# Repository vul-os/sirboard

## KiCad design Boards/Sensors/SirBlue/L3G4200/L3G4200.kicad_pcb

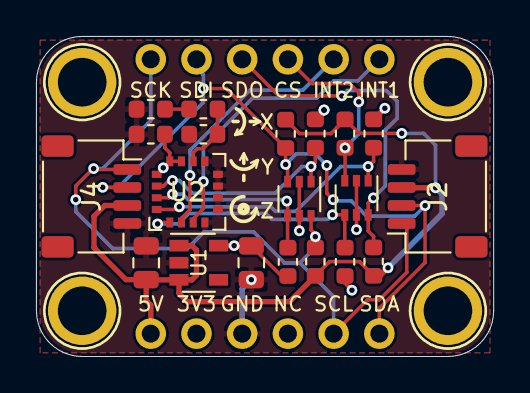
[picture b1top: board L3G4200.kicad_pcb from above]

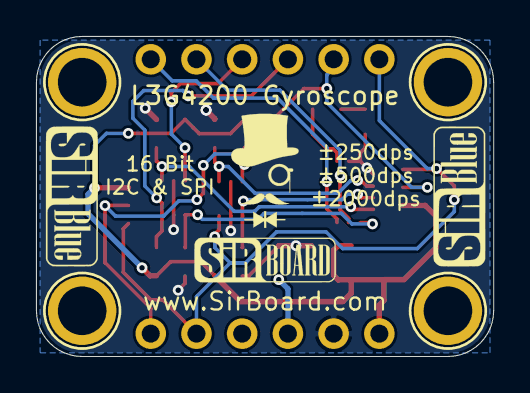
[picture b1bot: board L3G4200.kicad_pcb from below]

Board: 2 copper layers, 25.4 x 17.8 mm, 26 parts (2 on the bottom side), 15 nets.

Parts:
C1, C4: 10uF; C_0805_2012Metric
C2: 100nF; C_0603_1608Metric
C3: 10nF; C_0603_1608Metric
C5: 470nF; C_0603_1608Metric
H1, H2, H3, H4: MountingHole; MountingHole_M2.5_SirBoard
J1, J3: Conn_01x06; PinHeader_1x06_P2.54mm_Vertical
J2, J4: Conn_01x04; JST_SH_SM04B-SRSS-TB_1x04-1MP_P1.00mm_Horizontal
Q1, Q2: BSS138DW; SOT-363_SC-70-6
R1, R2, R3, R4, R5, R6, R7, R8, R9: 10K; R_0603_1608Metric
U1: AP2127K-3.3; SOT-23-5
U2: L3G4200; LGA-16_4x4mm_P0.65mm_LayoutBorder4x4y

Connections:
3V3: C2.1, C4.1, J1.2, Q1.2, Q1.5, Q2.2, Q2.5, R1.2, R3.2, R5.2, R7.2, U1.5, U2.1, U2.15, U2.16
5V: C1.1, J1.1, J2.3, J4.3, R2.1, R4.1, R6.1, R8.1, U1.1, U1.3
CS_3V3: Q1.4, R3.1, U2.5
CS_5V: J3.4, Q1.3, R4.2
DRDY: J3.5, U2.6
GND: C1.2, C2.2, C3.2, C4.2, J1.3, J2.4, J4.4, R9.2, U1.2, U2.8, U2.9, U2.10, U2.11, U2.12, U2.13
INT1: J3.6, U2.7
unnamed: C5.2, R9.1
PLL: C3.1, C5.1, U2.14
SCL_3V3: Q2.1, R5.1, U2.2
SCL_5V: J1.5, J2.1, J3.1, J4.1, Q2.6, R6.2
SDA_3V3: Q2.4, R7.1, U2.3
SDA_5V: J1.6, J2.2, J3.2, J4.2, Q2.3, R8.2
SDO_3V3: Q1.1, R1.1, U2.4
SDO_5V: J3.3, Q1.6, R2.2

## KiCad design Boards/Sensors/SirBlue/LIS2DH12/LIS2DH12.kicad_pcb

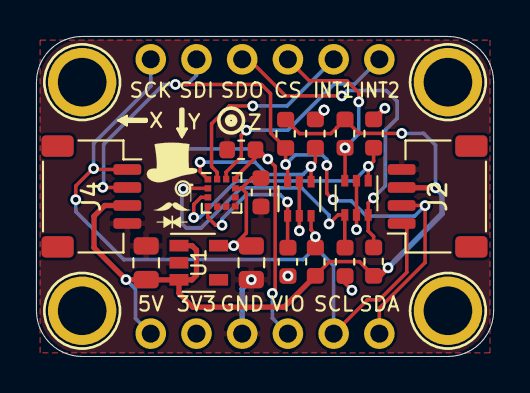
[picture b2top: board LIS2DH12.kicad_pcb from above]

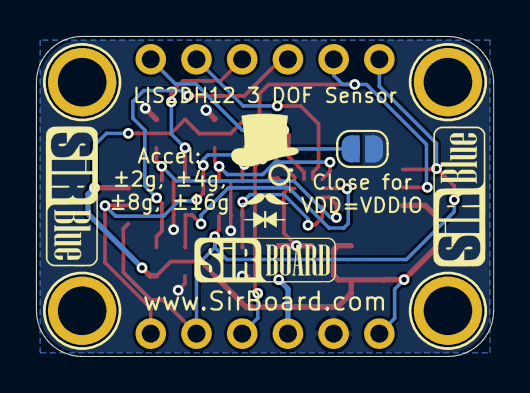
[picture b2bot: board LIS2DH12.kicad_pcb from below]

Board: 2 copper layers, 25.4 x 17.8 mm, 25 parts (3 on the bottom side), 14 nets.

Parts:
C1, C4: 10uF; C_0805_2012Metric
C3: 1uF; C_0603_1608Metric
C5: 100nF; C_0603_1608Metric
H1, H2, H3, H4: MountingHole; MountingHole_M2.5_SirBoard
J1, J3: Conn_01x06; PinHeader_1x06_P2.54mm_Vertical
J2, J4: Conn_01x04; JST_SH_SM04B-SRSS-TB_1x04-1MP_P1.00mm_Horizontal
JP1: SolderJumper_2_Open; SolderJumper-2_P1.3mm_Open_RoundedPad1.0x1.5mm
Q1, Q2: BSS138DW; SOT-363_SC-70-6
R1, R2, R3, R4, R5, R6, R7, R8: 10K; R_0603_1608Metric
U1: AP2127K-3.3; SOT-23-5
U2: LIS2HH12; LGA-12_2x2mm_P0.5mm

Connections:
3V3: C3.1, C4.1, J1.2, JP1.1, Q1.2, Q1.5, Q2.2, Q2.5, R1.2, R3.2, R5.2, R7.2, U1.5, U2.9
5V: C1.1, J1.1, J2.3, J4.3, R2.1, R4.1, R6.1, R8.1, U1.1, U1.3
CS_3V3: Q1.4, R3.1, U2.2
CS_5V: J3.4, Q1.3, R4.2
GND: C1.2, C3.2, C4.2, C5.2, J1.3, J2.4, J4.4, U1.2, U2.5, U2.6, U2.7, U2.8
INT1: J3.5, U2.12
INT2: J3.6, U2.11
SCL_3V3: Q2.1, R5.1, U2.1
SCL_5V: J1.5, J2.1, J3.1, J4.1, Q2.6, R6.2
SDA_3V3: Q2.4, R7.1, U2.4
SDA_5V: J1.6, J2.2, J3.2, J4.2, Q2.3, R8.2
SDO_3V3: Q1.1, R1.1, U2.3
SDO_5V: J3.3, Q1.6, R2.2
VDDIO: C5.1, J1.4, JP1.2, U2.10

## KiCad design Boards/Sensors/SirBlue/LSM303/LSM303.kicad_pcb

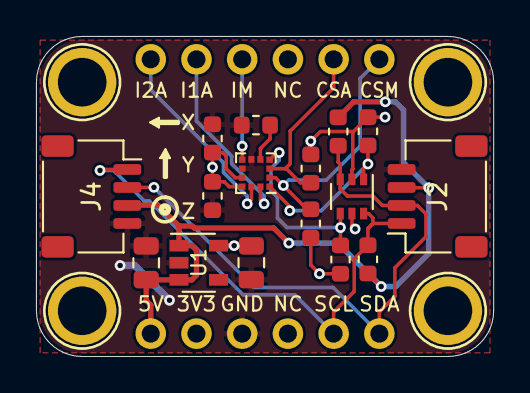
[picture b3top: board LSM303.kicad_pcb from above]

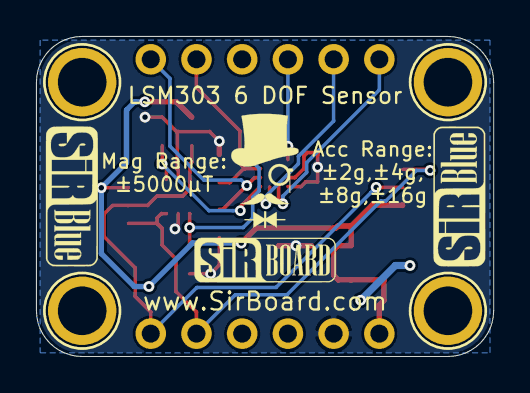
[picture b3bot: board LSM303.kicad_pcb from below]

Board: 2 copper layers, 25.4 x 17.8 mm, 22 parts (2 on the bottom side), 13 nets.

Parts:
C1, C4: 10uF; C_0805_2012Metric
C2: 220nF; C_0603_1608Metric
C3, C5: 100nF; C_0603_1608Metric
H1, H2, H3, H4: MountingHole; MountingHole_M2.5_SirBoard
J1, J3: Conn_01x06; PinHeader_1x06_P2.54mm_Vertical
J2, J4: Conn_01x04; JST_SH_SM04B-SRSS-TB_1x04-1MP_P1.00mm_Horizontal
Q2: BSS138DW; SOT-363_SC-70-6
R1, R2, R5, R6, R7, R8: 10K; R_0603_1608Metric
U1: AP2127K-3.3; SOT-23-5
U2: LSM303AGR; LGA-12_2x2mm_P0.5mm

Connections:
3V3: C3.1, C4.1, C5.1, J1.2, Q2.2, Q2.5, R1.1, R2.1, R5.2, R7.2, U1.5, U2.9, U2.10
5V: C1.1, J1.1, J2.3, J4.3, R6.1, R8.1, U1.1, U1.3
CS_MAG: J3.5, R2.2, U2.3
CS__XL: J3.6, R1.2, U2.2
GND: C1.2, C2.2, C3.2, C4.2, C5.2, J1.3, J2.4, J4.4, U1.2, U2.6, U2.8
INT1_XL: J3.2, U2.12
INT2_XL: J3.1, U2.11
INT_MAG: J3.3, U2.7
unnamed: C2.1, U2.5
SCL_3V3: Q2.1, R5.1, U2.1
SCL_5V: J1.5, J2.1, J4.1, Q2.6, R6.2
SDA_3V3: Q2.4, R7.1, U2.4
SDA_5V: J1.6, J2.2, J4.2, Q2.3, R8.2

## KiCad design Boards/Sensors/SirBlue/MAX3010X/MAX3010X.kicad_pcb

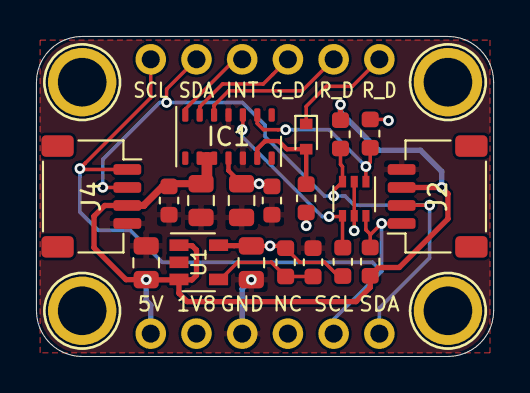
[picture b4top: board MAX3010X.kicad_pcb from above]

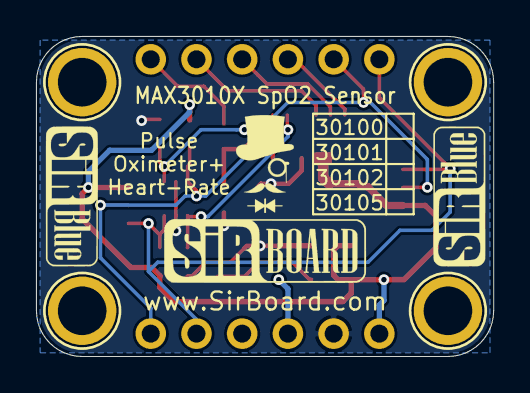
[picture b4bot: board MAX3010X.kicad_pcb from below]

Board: 2 copper layers, 25.4 x 17.8 mm, 25 parts (2 on the bottom side), 13 nets.

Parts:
C1, C4, C6: 10uF; C_0805_2012Metric
C2, C3: 100nF; C_0603_1608Metric
C5: 4.7uF; C_0805_2012Metric
D1: 1N4148WT-7; D_SOD-523
H1, H2, H3, H4: MountingHole; MountingHole_M2.5_SirBoard
IC1: MAX3010X; Maxim_OLGA-14_3.3x5.6mm_P0.8mm
J1, J3: Conn_01x06; PinHeader_1x06_P2.54mm_Vertical
J2, J4: Conn_01x04; JST_SH_SM04B-SRSS-TB_1x04-1MP_P1.00mm_Horizontal
Q1: BSS138DW; SOT-363_SC-70-6
R1, R5, R6, R7, R8: 4K7; R_0603_1608Metric
R2: 16K; R_0603_1608Metric
R3: 12K4; R_0603_1608Metric
U1: AP7365; SOT-23-5

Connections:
1V8: C2.1, C4.1, C5.1, IC1.11, J1.2, Q1.2, Q1.5, R2.1, R5.2, R7.2, R8.1, U1.5
5V: C1.1, C3.1, C6.1, IC1.9, IC1.10, J1.1, J2.3, J4.3, R1.1, R6.1, U1.1, U1.3
ADJ: R2.2, R3.1, U1.4
GND: C1.2, C2.2, C3.2, C4.2, C5.2, C6.2, IC1.4, IC1.12, J1.3, J2.4, J4.4, R3.2, U1.2
G_DRV: IC1.7, J3.3
INT_5V: D1.1, J3.6
IR_DRV: IC1.6, J3.4
unnamed: D1.2, IC1.13, R8.2
R_DRV: IC1.5, J3.5
SCL_1V8: IC1.2, Q1.1, R5.1
SCL_5V: J1.5, J2.1, J3.1, J4.1, Q1.6, R6.2
SDA_1V8: IC1.3, Q1.4, R7.1
SDA_5V: J1.6, J2.2, J3.2, J4.2, Q1.3, R1.2
